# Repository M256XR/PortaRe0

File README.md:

# PortaRe0

Cubie A7Z SBCベースのクラムシェル型ポータブルPC（Cyberdeck）自作プロジェクト。

## 概要

| 項目 | 内容 |
|------|------|
| SBC | Cubie A7Z (Allwinner A733 / 8コア / WiFi6 / BT5.4) |
| ディスプレイ | 5.5" Sharp LS055R1SX04 (1440×2560 / MIPI DSI) |
| キーボード | カスタムPCB + Alps SKRPABE010 × 64キー / RP2040 / QMK |
| 入力 | 3DSスライドパッド（アナログスティック） |
| 電源 | LiPo 606090 (4200mAh) + BQ25895 充電IC + TPS61023 昇圧DC-DC ×2 |
| USBハブ | VL812 (USB 3.0 / 4ポート) |
| ストレージ | M.2 2230 NVMe SSD（PCIe Gen3 x1 / Cubie A7Z F0506-16-BGR経由） |
| オーディオ | MAX98357A × 2 (スピーカー I2S) / PCM5102A + TPA6132A2 (イヤホン DAC+アンプ) |
| MCU | RP2040 × 2（キーボード専用 / オーディオ専用） |
| PCB | 6層基板 / JLCPCB PCBA |
| 筐体 | 3Dプリンター自作（クラムシェル / 139×81mm） |

## 現在のフェーズ

**Phase 3: PCBレイアウト完了 → 発注準備完了（資金準備待ち）**

- [x] power シート（BQ25895 / TPS61023 ×2 / AP2112K）
- [x] usb_hub シート（VL812 / W25Q32 / J_EXT_C / J_EXT_A）
- [x] keyboard シート（RP2040 #1 / キーマトリクス / アナログスティック / LED）
- [x] audio シート（RP2040 #2 / MAX98357A ×2 / PCM5102A / TPA6132A2）
- [x] connectors シート（J_HDMI_CTRL / J_FAN）
- [x] hdmi_adapter シート（別基板 / Micro HDMI → FFC変換）
- [x] usb_adapter シート（別基板 / FPCスティフナー + USB-Cオス ×2）
- [x] m2_ssd シート（M.2 2230 NVMe / PCIe Gen3 x1 / RT9080 LDO）
- [x] ERC（HP系のみ残存 / 想定内）
- [x] ガーバー生成済み / CPL生成済み
- [ ] JLCPCB発注（資金準備後）

## ドキュメント

- [Claude/PROGRESS.md](./Claude/PROGRESS.md) - 現在の進捗・次のタスク
- [Claude/CLAUDE.md](./Claude/CLAUDE.md) - 仕様サマリ・セッション開始手順
- [Claude/specs/](./Claude/specs/) - ハードウェア詳細仕様（電源・キーボード・オーディオ・M.2）
- [bom/cyberdeck_bom.xlsx](./bom/cyberdeck_bom.xlsx) - BOM (Excel)
- [bom/cyberdeck_bom.csv](./bom/cyberdeck_bom.csv) - BOM (CSV)
- [keyboard/matrix.md](./keyboard/matrix.md) - キーマトリクス割り当て表
- [keyboard/info.json](./keyboard/info.json) - QMKレイアウト定義

## リポジトリ構成

```
kicad/PortaRe0/        KiCadプロジェクト（回路図・PCB）
kicad/PortaRe0_lib/    カスタムシンボル・フットプリント・3Dモデル
keyboard/              キーレイアウト・マトリクス定義・QMK設定
cad/                   筐体 3Dデータ（進行中）
docs/                  データシート
bom/                   BOM（xlsx / csv）
Claude/                設計ドキュメント・進捗ログ・セッションログ
```

## 主要部品 C番号一覧

| 部品 | 型番 | C番号 |
|------|------|-------|
| 充電IC | BQ25895RTWR | C80200 |
| 昇圧DC-DC | TPS61023DRLR | C919459 |
| LDO 3.3V | AP2112K-3.3TRG1 | C51118 |
| USB HUBチップ | VL812-Q7 | C69417 |
| SPI Flash | W25Q32JVSSIQ | C82344 |
| MCU | RP2040 | C2040 |
| クリスタル（RP2040用 12MHz） | X322512MOB4SI | C70565 |
| クリスタル（VL812用 25MHz） | X322525MOB4SI | C9006 |
| I2Sアンプ | MAX98357AEWL+T | C2682619 |
| イヤホン用DAC | PCM5102APWR | C107671 |
| ヘッドフォンアンプ | TPA6132A2RTER | C69901 |
| USBパワースイッチ | TPS2042BDR | C138720 |
| USB ESD保護 | USBLC6-2SC6 | C7519 |
| キースイッチ | Alps SKRPABE010 | C115360 |
| ダイオード | 1N4148W | C2099 |
| MOSFET（レベル変換 / ファン制御） | BSS138 | C52895 |
| ショットキーダイオード（EN保護） | BAT54 | C466635 |
| FPCコネクタ（スティック用） | Molex 5034800440 | C3170007 |
| ZIF FPCコネクタ 24pin | FPC-05F-24PH20 | C2856805 |
| ZIF FPCコネクタ 16pin（PCIe） | FPC-05F-16PH20 | C2856801 |
| M.2ソケット（M-key 2230） | NASM0-S6701-TP40 | C367029 |
| LDO 3.3V（M.2用） | RT9080-33GJ5 | C841192 |
| USB-C レセプタクル（外部） | USB31-TYPE-C-FSABC | C2880583 |
| USB-A レセプタクル（外部） | HC-USB3.0-L168-WP | C7501850 |
| USB-C オス SMD（SBC接続） | 918-118A2021Y40000 | C168690 |

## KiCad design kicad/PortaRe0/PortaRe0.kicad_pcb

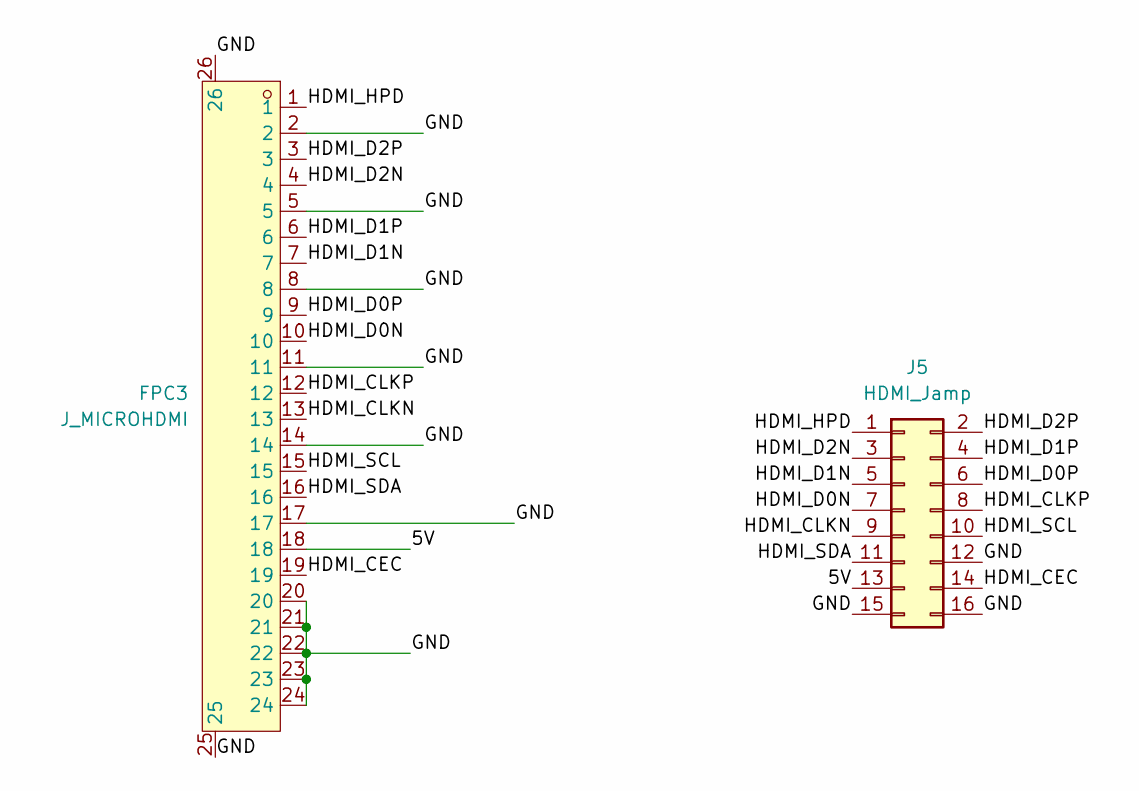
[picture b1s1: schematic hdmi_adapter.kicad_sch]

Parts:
FPC3: J_MICROHDMI; FPC-SMD_24P-P0.50_FPC-05F-24PH20; LCSC Part C2856805
J5: HDMI_Jamp; PinHeader_2x08_P2.00mm_Vertical

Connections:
unnamed: FPC3.1, J5.1
unnamed: FPC3.3, J5.2
unnamed: FPC3.4, J5.3
unnamed: FPC3.6, J5.4
unnamed: FPC3.7, J5.5
unnamed: FPC3.9, J5.6
unnamed: FPC3.10, J5.7
unnamed: FPC3.2, FPC3.5, FPC3.8, FPC3.11, FPC3.14, FPC3.17, FPC3.20, FPC3.21, FPC3.22, FPC3.23, FPC3.24, FPC3.25, FPC3.26, J5.12, J5.15, J5.16
unnamed: FPC3.12, J5.8
unnamed: FPC3.13, J5.9
unnamed: FPC3.15, J5.10
unnamed: FPC3.16, J5.11
unnamed: FPC3.18, J5.13
unnamed: FPC3.19, J5.14

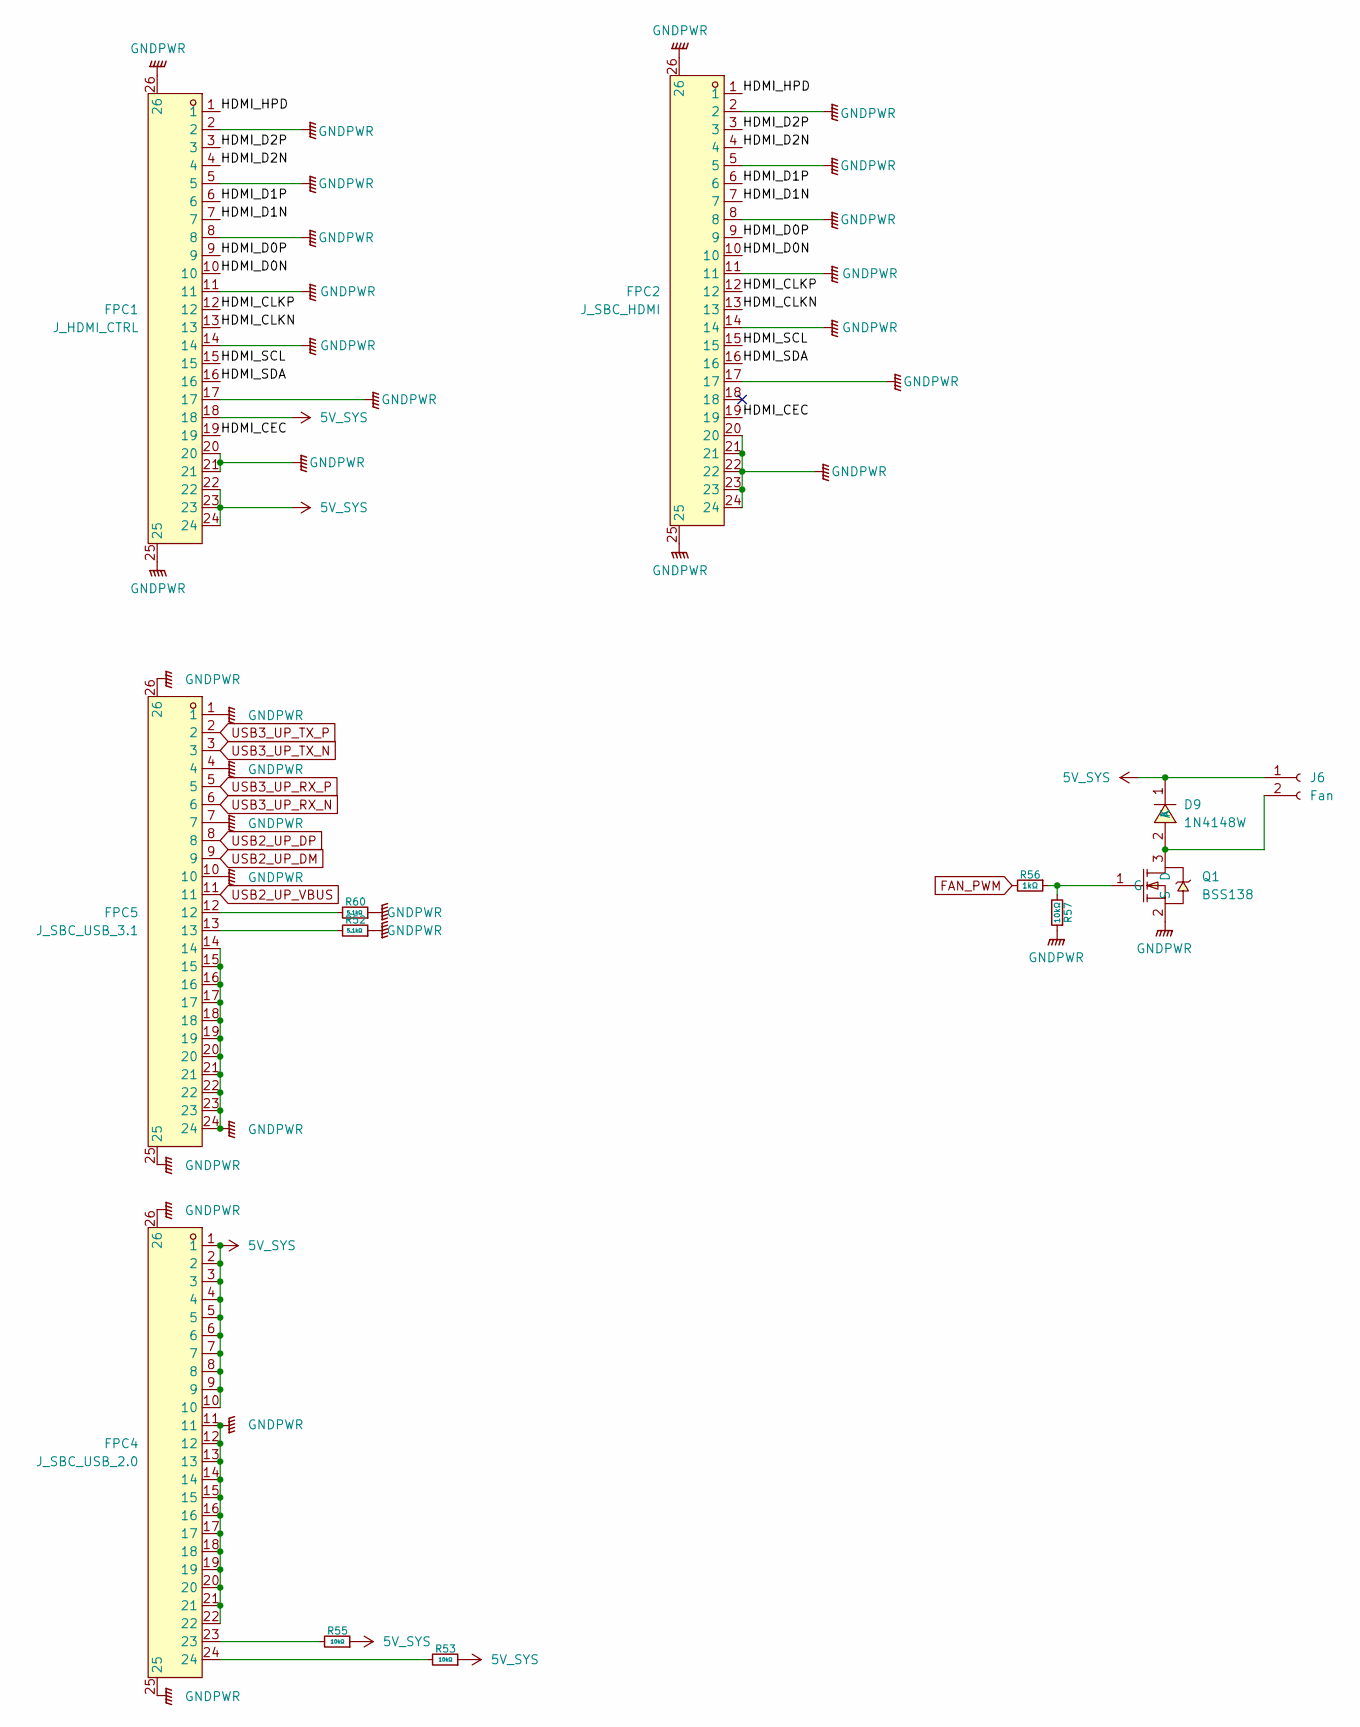
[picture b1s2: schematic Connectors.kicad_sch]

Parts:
D9: 1N4148W; SOD-123_L2.8-W1.8-LS3.7-RD; LCSC Part C2099
FPC1: J_HDMI_CTRL; FPC-SMD_24P-P0.50_FPC-05F-24PH20; LCSC Part C2856805
FPC2: J_SBC_HDMI; FPC-SMD_24P-P0.50_FPC-05F-24PH20; LCSC Part C2856805
FPC4: J_SBC_USB_2.0; FPC-SMD_24P-P0.50_FPC-05F-24PH20; LCSC Part C2856805
FPC5: J_SBC_USB_3.1; FPC-SMD_24P-P0.50_FPC-05F-24PH20; LCSC Part C2856805
J6: Fan; CONN-TH_S2B-PH-K-S-LF-SN
Q1: BSS138; SOT-23-3_L2.9-W1.6-P1.90-LS2.8-BR; LCSC Part C52895
R52, R60: 5.1kΩ; R_0402_1005Metric
R53, R55, R57: 10kΩ; R_0402_1005Metric
R56: 1kΩ; R_0402_1005Metric

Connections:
5V_SYS: D9.1 (K), FPC1.18, FPC1.22, FPC1.23, FPC1.24, FPC4.1, FPC4.2, FPC4.3, FPC4.4, FPC4.5, FPC4.6, FPC4.7, FPC4.8, FPC4.9, FPC4.10, J6.1, R53.1, R55.1; also elsewhere on the board
FAN_PWM: R56.2; also elsewhere on the board
GND: FPC1.2, FPC1.5, FPC1.8, FPC1.11, FPC1.14, FPC1.17, FPC1.20, FPC1.21, FPC1.25, FPC1.26, FPC2.2, FPC2.5, FPC2.8, FPC2.11, FPC2.14, FPC2.17, FPC2.20, FPC2.21, FPC2.22, FPC2.23, FPC2.24, FPC2.25, FPC2.26, FPC4.11, FPC4.12, FPC4.13, FPC4.14, FPC4.15, FPC4.16, FPC4.17, FPC4.18, FPC4.19, FPC4.20, FPC4.21, FPC4.22, FPC4.25, FPC4.26, FPC5.1, FPC5.4, FPC5.7, FPC5.10, FPC5.14, FPC5.15, FPC5.16, FPC5.17, FPC5.18, FPC5.19, FPC5.20, FPC5.21, FPC5.22, FPC5.23, FPC5.24, FPC5.25, FPC5.26, Q1.2 (S), R52.1, R57.1, R60.1; also elsewhere on the board
unnamed 109: D9.2 (A), J6.2, Q1.3 (D); also elsewhere on the board
unnamed: FPC1.1, FPC2.1
unnamed: FPC1.3, FPC2.3
unnamed: FPC1.4, FPC2.4
unnamed: FPC1.6, FPC2.6
unnamed: FPC1.7, FPC2.7
unnamed: FPC1.9, FPC2.9
unnamed: FPC1.10, FPC2.10
unnamed: FPC1.12, FPC2.12
unnamed: FPC1.13, FPC2.13
unnamed: FPC1.15, FPC2.15
unnamed: FPC1.16, FPC2.16
unnamed: FPC1.19, FPC2.19
unnamed 136: FPC4.23, R55.2; also elsewhere on the board
unnamed 137: FPC4.24, R53.2; also elsewhere on the board
unnamed 138: FPC5.12, R60.2; also elsewhere on the board
unnamed 139: FPC5.13, R52.2; also elsewhere on the board
unnamed: Q1.1 (G), R56.1, R57.2

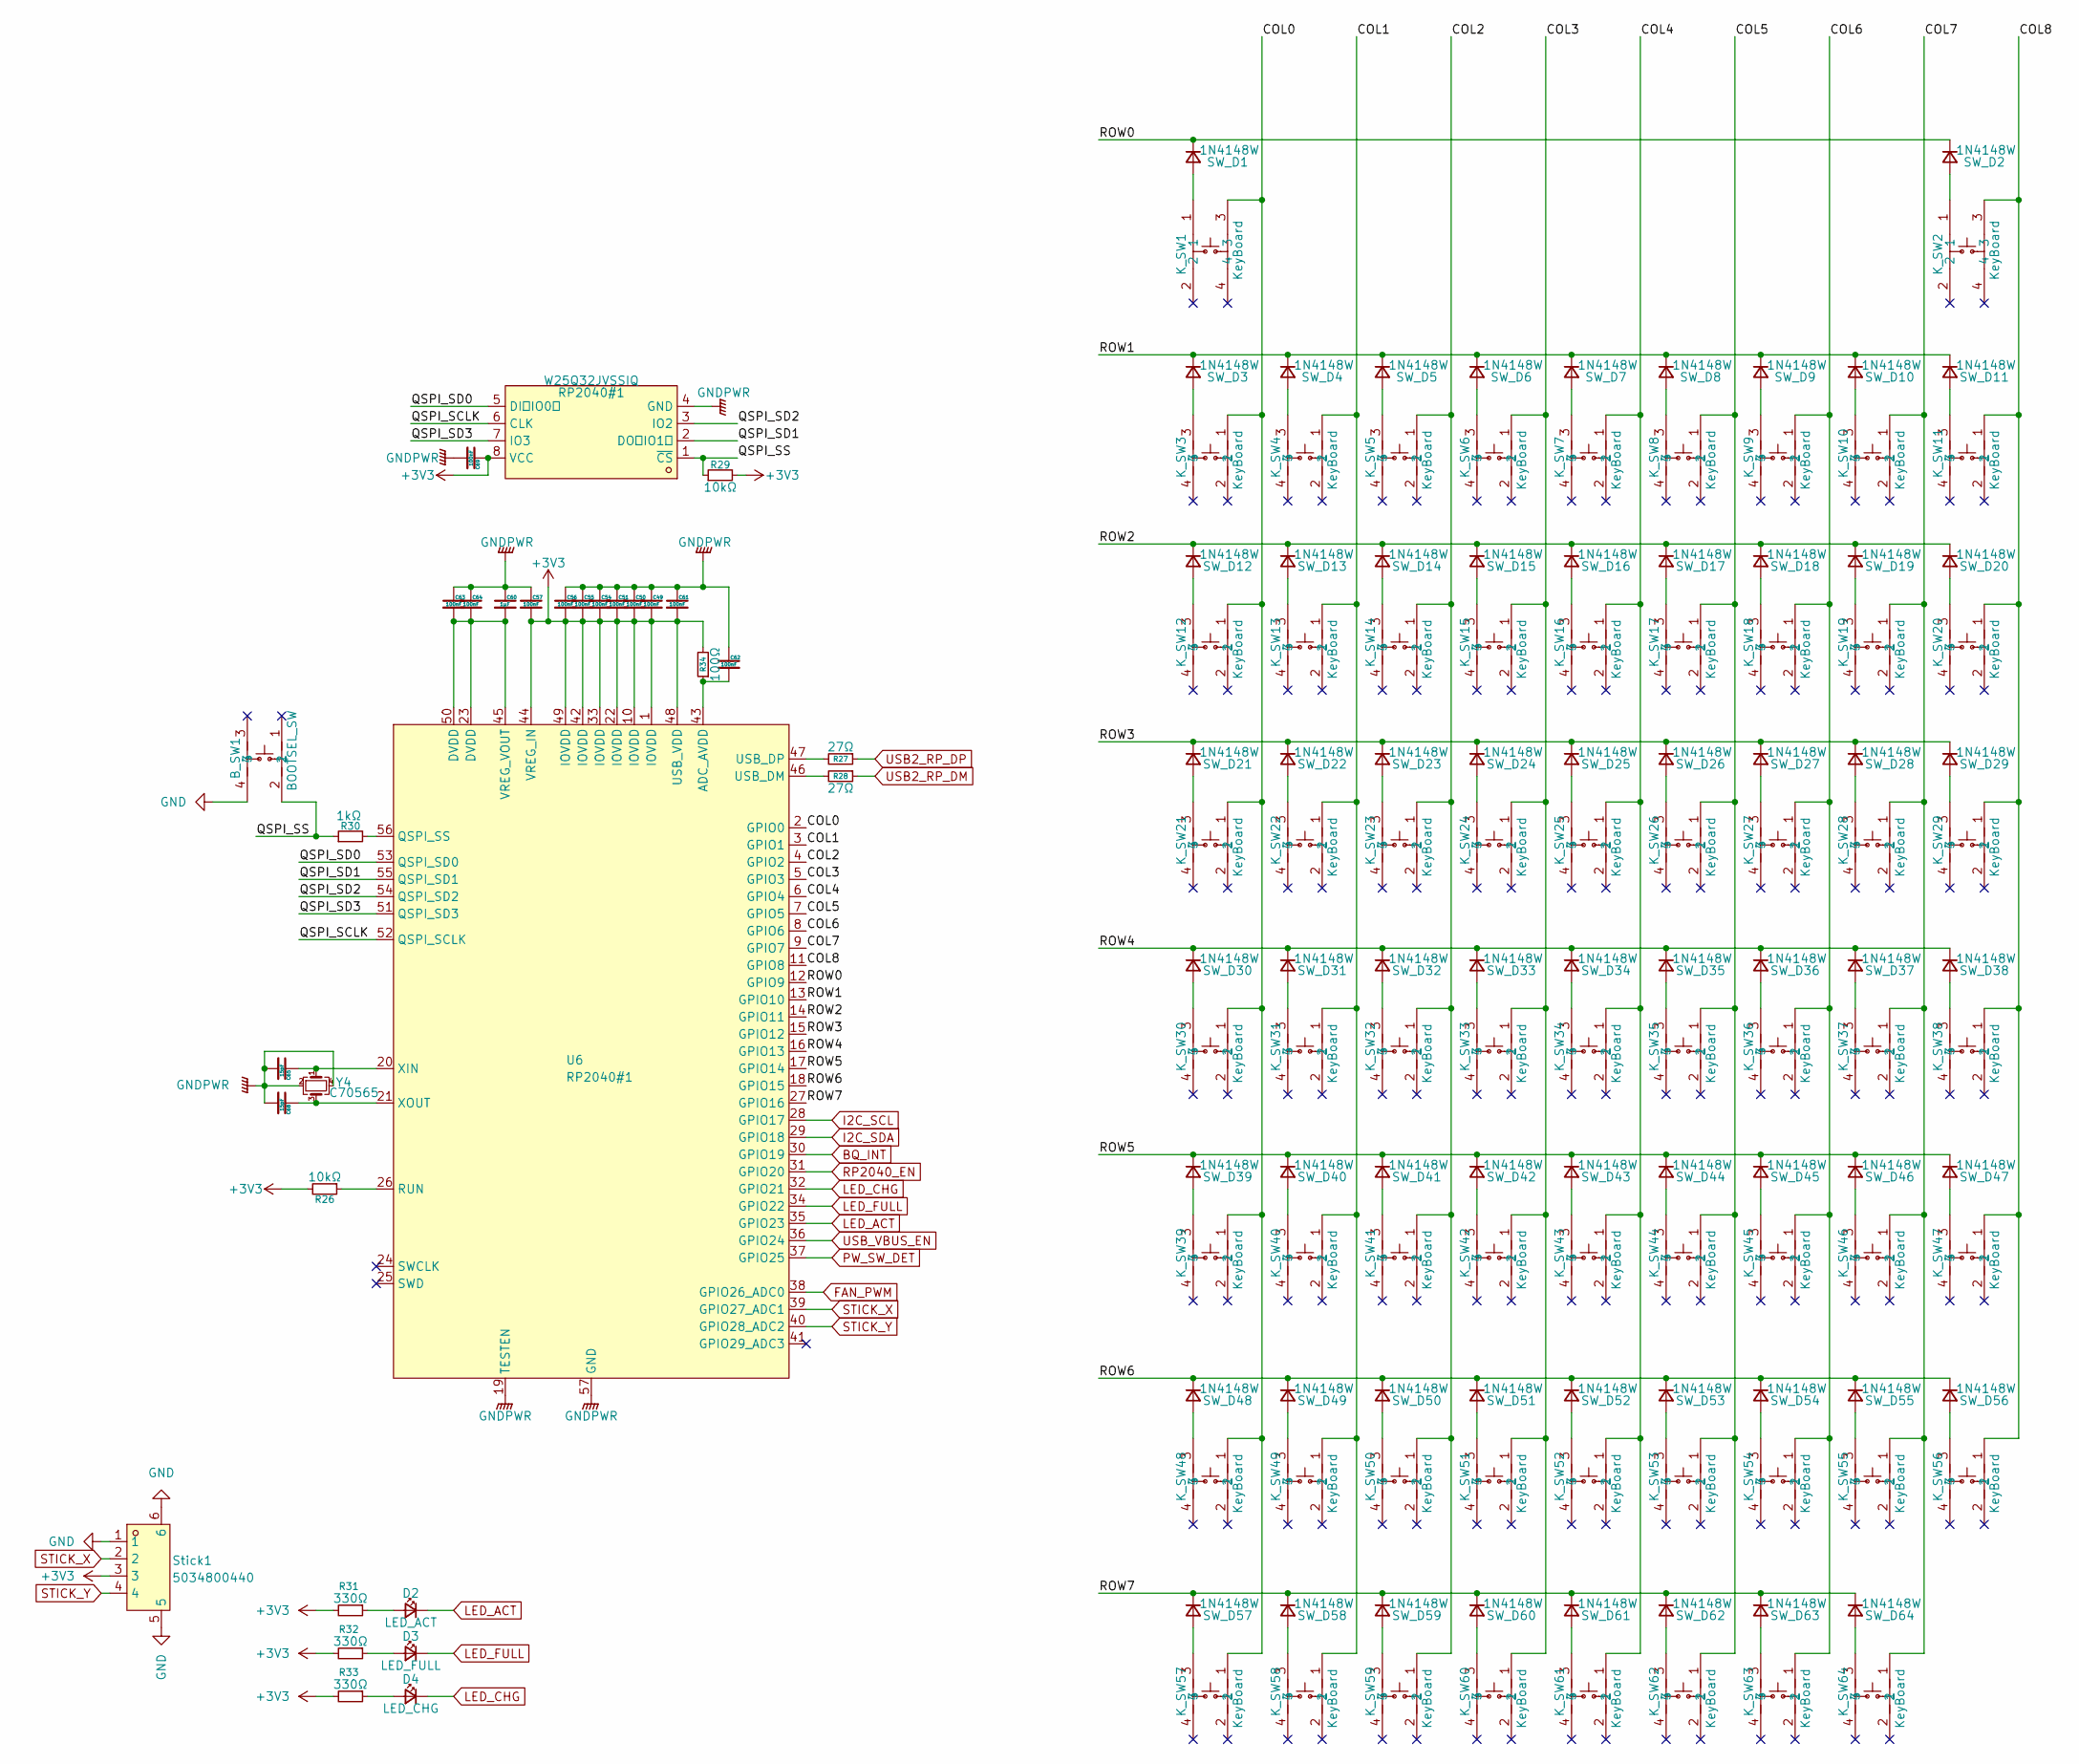
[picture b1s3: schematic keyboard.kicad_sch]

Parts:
B_SW1: BOOTSEL_SW; KEY-SMD_4P-L4.2-W3.2-P2.20-LS4.6; LCSC Part C115360
C49, C50, C51, C54, C55, C56, C57, C61, C62, C63, C64, C69: 100nF; C_0402_1005Metric
C60: 1μF; C_0402_1005Metric
C65, C68: 15pF; C_0402_1005Metric
D2: LED_ACT; LED_0603_1608Metric
D3: LED_FULL; LED_0603_1608Metric
D4: LED_CHG; LED_0603_1608Metric
K_SW1, K_SW2: KeyBoard; KEY-SMD_4P-SKSCLXX010; LCSC Part C115361
K_SW3, K_SW4, K_SW5, K_SW6, K_SW7, K_SW8, K_SW9, K_SW10, K_SW11, K_SW12, K_SW13, K_SW14, K_SW15, K_SW16, K_SW17, K_SW18, K_SW19, K_SW20, K_SW21, K_SW22, K_SW23, K_SW24, K_SW25, K_SW26, K_SW27, K_SW28, K_SW29, K_SW30, K_SW31, K_SW32, K_SW33, K_SW34, K_SW35, K_SW36, K_SW37, K_SW38, K_SW39, K_SW40, K_SW41, K_SW42, K_SW43, K_SW44, K_SW45, K_SW46, K_SW47, K_SW48, K_SW49, K_SW50, K_SW51, K_SW52, K_SW53, K_SW54, K_SW55, K_SW56, K_SW57, K_SW58, K_SW59, K_SW60, K_SW61, K_SW62, K_SW63, K_SW64: KeyBoard; KEY-SMD_4P-L4.2-W3.2-P2.20-LS4.6; LCSC Part C115360
R26, R29: 10kΩ; R_0402_1005Metric
R27, R28: 27Ω; R_0603_1608Metric
R30: 1kΩ; R_0402_1005Metric
R31, R32, R33: 330Ω; R_0402_1005Metric
R34: 100Ω; R_0402_1005Metric
RP2040#1: W25Q32JVSSIQ; SOIC-8_L5.3-W5.3-P1.27-LS8.0-BL; LCSC Part C82344
SW_D1, SW_D2, SW_D3, SW_D4, SW_D5, SW_D6, SW_D7, SW_D8, SW_D9, SW_D10, SW_D11, SW_D12, SW_D13, SW_D14, SW_D15, SW_D16, SW_D17, SW_D18, SW_D19, SW_D20, SW_D21, SW_D22, SW_D23, SW_D24, SW_D25, SW_D26, SW_D27, SW_D28, SW_D29, SW_D30, SW_D31, SW_D32, SW_D33, SW_D34, SW_D35, SW_D36, SW_D37, SW_D38, SW_D39, SW_D40, SW_D41, SW_D42, SW_D43, SW_D44, SW_D45, SW_D46, SW_D47, SW_D48, SW_D49, SW_D50, SW_D51, SW_D52, SW_D53, SW_D54, SW_D55, SW_D56, SW_D57, SW_D58, SW_D59, SW_D60, SW_D61, SW_D62, SW_D63, SW_D64: 1N4148W; SOD-123_L2.8-W1.8-LS3.7-RD
Stick1: 5034800440; FPC-SMD_5034800400; LCSC Part C3170007
U6: RP2040#1; LQFN-56_L7.0-W7.0-P0.4-EP; LCSC Part C2040
Y4: C70565; CRYSTAL-SMD_4P-L3.2-W2.5-BL

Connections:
+3V3: C49.2, C50.2, C51.2, C54.2, C55.2, C56.2, C57.2, C61.2, C69.1, R26.2, R29.2, R31.2, R32.2, R33.2, R34.2, RP2040#1.8 (VCC), Stick1.3, U6.1 (IOVDD), U6.10 (IOVDD), U6.22 (IOVDD), U6.33 (IOVDD), U6.42 (IOVDD), U6.44 (VREG_IN), U6.48 (USB_VDD), U6.49 (IOVDD); also elsewhere on the board
/keyboard/COL0: K_SW1.3, K_SW3.1, K_SW12.1, K_SW21.1, K_SW30.1, K_SW39.1, K_SW48.1, K_SW57.1, U6.2 (GPIO0)
/keyboard/COL1: K_SW4.1, K_SW13.1, K_SW22.1, K_SW31.1, K_SW40.1, K_SW49.1, K_SW58.1, U6.3 (GPIO1)
/keyboard/COL2: K_SW5.1, K_SW14.1, K_SW23.1, K_SW32.1, K_SW41.1, K_SW50.1, K_SW59.1, U6.4 (GPIO2)
/keyboard/COL3: K_SW6.1, K_SW15.1, K_SW24.1, K_SW33.1, K_SW42.1, K_SW51.1, K_SW60.1, U6.5 (GPIO3)
/keyboard/COL4: K_SW7.1, K_SW16.1, K_SW25.1, K_SW34.1, K_SW43.1, K_SW52.1, K_SW61.1, U6.6 (GPIO4)
/keyboard/COL5: K_SW8.1, K_SW17.1, K_SW26.1, K_SW35.1, K_SW44.1, K_SW53.1, K_SW62.1, U6.7 (GPIO5)
/keyboard/COL6: K_SW9.1, K_SW18.1, K_SW27.1, K_SW36.1, K_SW45.1, K_SW54.1, K_SW63.1, U6.8 (GPIO6)
/keyboard/COL7: K_SW10.1, K_SW19.1, K_SW28.1, K_SW37.1, K_SW46.1, K_SW55.1, K_SW64.1, U6.9 (GPIO7)
/keyboard/COL8: K_SW2.3, K_SW11.1, K_SW20.1, K_SW29.1, K_SW38.1, K_SW47.1, K_SW56.1, U6.11 (GPIO8)
/keyboard/QSPI_SCLK: RP2040#1.6 (CLK), U6.52 (QSPI_SCLK)
/keyboard/QSPI_SD0: RP2040#1.5 (DI（IO0）), U6.53 (QSPI_SD0)
/keyboard/QSPI_SD1: RP2040#1.2 (DO（IO1）), U6.55 (QSPI_SD1)
/keyboard/QSPI_SD2: RP2040#1.3 (IO2), U6.54 (QSPI_SD2)
/keyboard/QSPI_SD3: RP2040#1.7 (IO3), U6.51 (QSPI_SD3)
/keyboard/QSPI_SS: B_SW1.2, R29.1, R30.1, RP2040#1.1 (~CS)
/keyboard/ROW0: SW_D1.1 (K), SW_D2.1 (K), U6.12 (GPIO9)
/keyboard/ROW1: SW_D3.1 (K), SW_D4.1 (K), SW_D5.1 (K), SW_D6.1 (K), SW_D7.1 (K), SW_D8.1 (K), SW_D9.1 (K), SW_D10.1 (K), SW_D11.1 (K), U6.13 (GPIO10)
/keyboard/ROW2: SW_D12.1 (K), SW_D13.1 (K), SW_D14.1 (K), SW_D15.1 (K), SW_D16.1 (K), SW_D17.1 (K), SW_D18.1 (K), SW_D19.1 (K), SW_D20.1 (K), U6.14 (GPIO11)
/keyboard/ROW3: SW_D21.1 (K), SW_D22.1 (K), SW_D23.1 (K), SW_D24.1 (K), SW_D25.1 (K), SW_D26.1 (K), SW_D27.1 (K), SW_D28.1 (K), SW_D29.1 (K), U6.15 (GPIO12)
/keyboard/ROW4: SW_D30.1 (K), SW_D31.1 (K), SW_D32.1 (K), SW_D33.1 (K), SW_D34.1 (K), SW_D35.1 (K), SW_D36.1 (K), SW_D37.1 (K), SW_D38.1 (K), U6.16 (GPIO13)
/keyboard/ROW5: SW_D39.1 (K), SW_D40.1 (K), SW_D41.1 (K), SW_D42.1 (K), SW_D43.1 (K), SW_D44.1 (K), SW_D45.1 (K), SW_D46.1 (K), SW_D47.1 (K), U6.17 (GPIO14)
/keyboard/ROW6: SW_D48.1 (K), SW_D49.1 (K), SW_D50.1 (K), SW_D51.1 (K), SW_D52.1 (K), SW_D53.1 (K), SW_D54.1 (K), SW_D55.1 (K), SW_D56.1 (K), U6.18 (GPIO15)
/keyboard/ROW7: SW_D57.1 (K), SW_D58.1 (K), SW_D59.1 (K), SW_D60.1 (K), SW_D61.1 (K), SW_D62.1 (K), SW_D63.1 (K), SW_D64.1 (K), U6.27 (GPIO16)
BQ_INT: U6.30 (GPIO19); also elsewhere on the board
FAN_PWM: U6.38 (GPIO26_ADC0); also elsewhere on the board
GND: B_SW1.4, C49.1, C50.1, C51.1, C54.1, C55.1, C56.1, C57.1, C60.1, C61.1, C62.1, C63.1, C64.1, C65.2, C68.2, C69.2, RP2040#1.4 (GND), Stick1.1, Stick1.5, Stick1.6, U6.19 (TESTEN), U6.57 (GND), Y4.2, Y4.4; also elsewhere on the board
I2C_SCL: U6.28 (GPIO17); also elsewhere on the board
I2C_SDA: U6.29 (GPIO18); also elsewhere on the board
LED_ACT: D2.1 (K), U6.35 (GPIO23)
LED_CHG: D4.1 (K), U6.32 (GPIO21)
LED_FULL: D3.1 (K), U6.34 (GPIO22)
unnamed: D2.2 (A), R31.1
unnamed: D3.2 (A), R32.1
unnamed: D4.2 (A), R33.1
unnamed: K_SW1.1, SW_D1.2 (A)
unnamed: K_SW2.1, SW_D2.2 (A)
unnamed: K_SW3.3, SW_D3.2 (A)
unnamed: K_SW4.3, SW_D4.2 (A)
unnamed: K_SW5.3, SW_D5.2 (A)
unnamed: K_SW6.3, SW_D6.2 (A)
unnamed: K_SW7.3, SW_D7.2 (A)
unnamed: K_SW8.3, SW_D8.2 (A)
unnamed: K_SW9.3, SW_D9.2 (A)
unnamed: K_SW10.3, SW_D10.2 (A)
unnamed: K_SW11.3, SW_D11.2 (A)
unnamed: K_SW12.3, SW_D12.2 (A)
unnamed: K_SW13.3, SW_D13.2 (A)
unnamed: K_SW14.3, SW_D14.2 (A)
unnamed: K_SW15.3, SW_D15.2 (A)
unnamed: K_SW16.3, SW_D16.2 (A)
unnamed: K_SW17.3, SW_D17.2 (A)
unnamed: K_SW18.3, SW_D18.2 (A)
unnamed: K_SW19.3, SW_D19.2 (A)
unnamed: K_SW20.3, SW_D20.2 (A)
unnamed: K_SW21.3, SW_D21.2 (A)
unnamed: K_SW22.3, SW_D22.2 (A)
unnamed: K_SW23.3, SW_D23.2 (A)
unnamed: K_SW24.3, SW_D24.2 (A)
unnamed: K_SW25.3, SW_D25.2 (A)
unnamed: K_SW26.3, SW_D26.2 (A)
unnamed: K_SW27.3, SW_D27.2 (A)
unnamed: K_SW28.3, SW_D28.2 (A)
unnamed: K_SW29.3, SW_D29.2 (A)
unnamed: K_SW30.3, SW_D30.2 (A)
unnamed: K_SW31.3, SW_D31.2 (A)
unnamed: K_SW32.3, SW_D32.2 (A)
unnamed: K_SW33.3, SW_D33.2 (A)
unnamed: K_SW34.3, SW_D34.2 (A)
unnamed: K_SW35.3, SW_D35.2 (A)
unnamed: K_SW36.3, SW_D36.2 (A)
unnamed: K_SW37.3, SW_D37.2 (A)
unnamed: K_SW38.3, SW_D38.2 (A)
unnamed: K_SW39.3, SW_D39.2 (A)
unnamed: K_SW40.3, SW_D40.2 (A)
unnamed: K_SW41.3, SW_D41.2 (A)
unnamed: K_SW42.3, SW_D42.2 (A)
unnamed: K_SW43.3, SW_D43.2 (A)
unnamed: K_SW44.3, SW_D44.2 (A)
unnamed: K_SW45.3, SW_D45.2 (A)
unnamed: K_SW46.3, SW_D46.2 (A)
unnamed: K_SW47.3, SW_D47.2 (A)
unnamed: K_SW48.3, SW_D48.2 (A)
unnamed: K_SW49.3, SW_D49.2 (A)
unnamed: K_SW50.3, SW_D50.2 (A)
unnamed: K_SW51.3, SW_D51.2 (A)
unnamed: K_SW52.3, SW_D52.2 (A)
unnamed: K_SW53.3, SW_D53.2 (A)
unnamed: K_SW54.3, SW_D54.2 (A)
unnamed: K_SW55.3, SW_D55.2 (A)
unnamed: K_SW56.3, SW_D56.2 (A)
unnamed: K_SW57.3, SW_D57.2 (A)
unnamed: K_SW58.3, SW_D58.2 (A)
unnamed: K_SW59.3, SW_D59.2 (A)
unnamed: K_SW60.3, SW_D60.2 (A)
unnamed: K_SW61.3, SW_D61.2 (A)
unnamed: K_SW62.3, SW_D62.2 (A)
unnamed: K_SW63.3, SW_D63.2 (A)
unnamed: K_SW64.3, SW_D64.2 (A)
unnamed: C62.2, R34.1, U6.43 (ADC_AVDD)
unnamed: R30.2, U6.56 (QSPI_SS)
unnamed: R26.1, U6.26 (RUN)
unnamed: R28.2, U6.46 (USB_DM)
unnamed: R27.2, U6.47 (USB_DP)
unnamed: C60.2, C63.2, C64.2, U6.23 (DVDD), U6.45 (VREG_VOUT), U6.50 (DVDD)
unnamed: C65.1, U6.20 (XIN), Y4.1
unnamed: C68.1, U6.21 (XOUT), Y4.3
PW_SW_DET: U6.37 (GPIO25); also elsewhere on the board
RP2040_EN: U6.31 (GPIO20); also elsewhere on the board
STICK_X: Stick1.2, U6.39 (GPIO27_ADC1); also elsewhere on the board
STICK_Y: Stick1.4, U6.40 (GPIO28_ADC2); also elsewhere on the board
USB2_RP_DM: R28.1; also elsewhere on the board
USB2_RP_DP: R27.1; also elsewhere on the board
USB_VBUS_EN: U6.36 (GPIO24); also elsewhere on the board
